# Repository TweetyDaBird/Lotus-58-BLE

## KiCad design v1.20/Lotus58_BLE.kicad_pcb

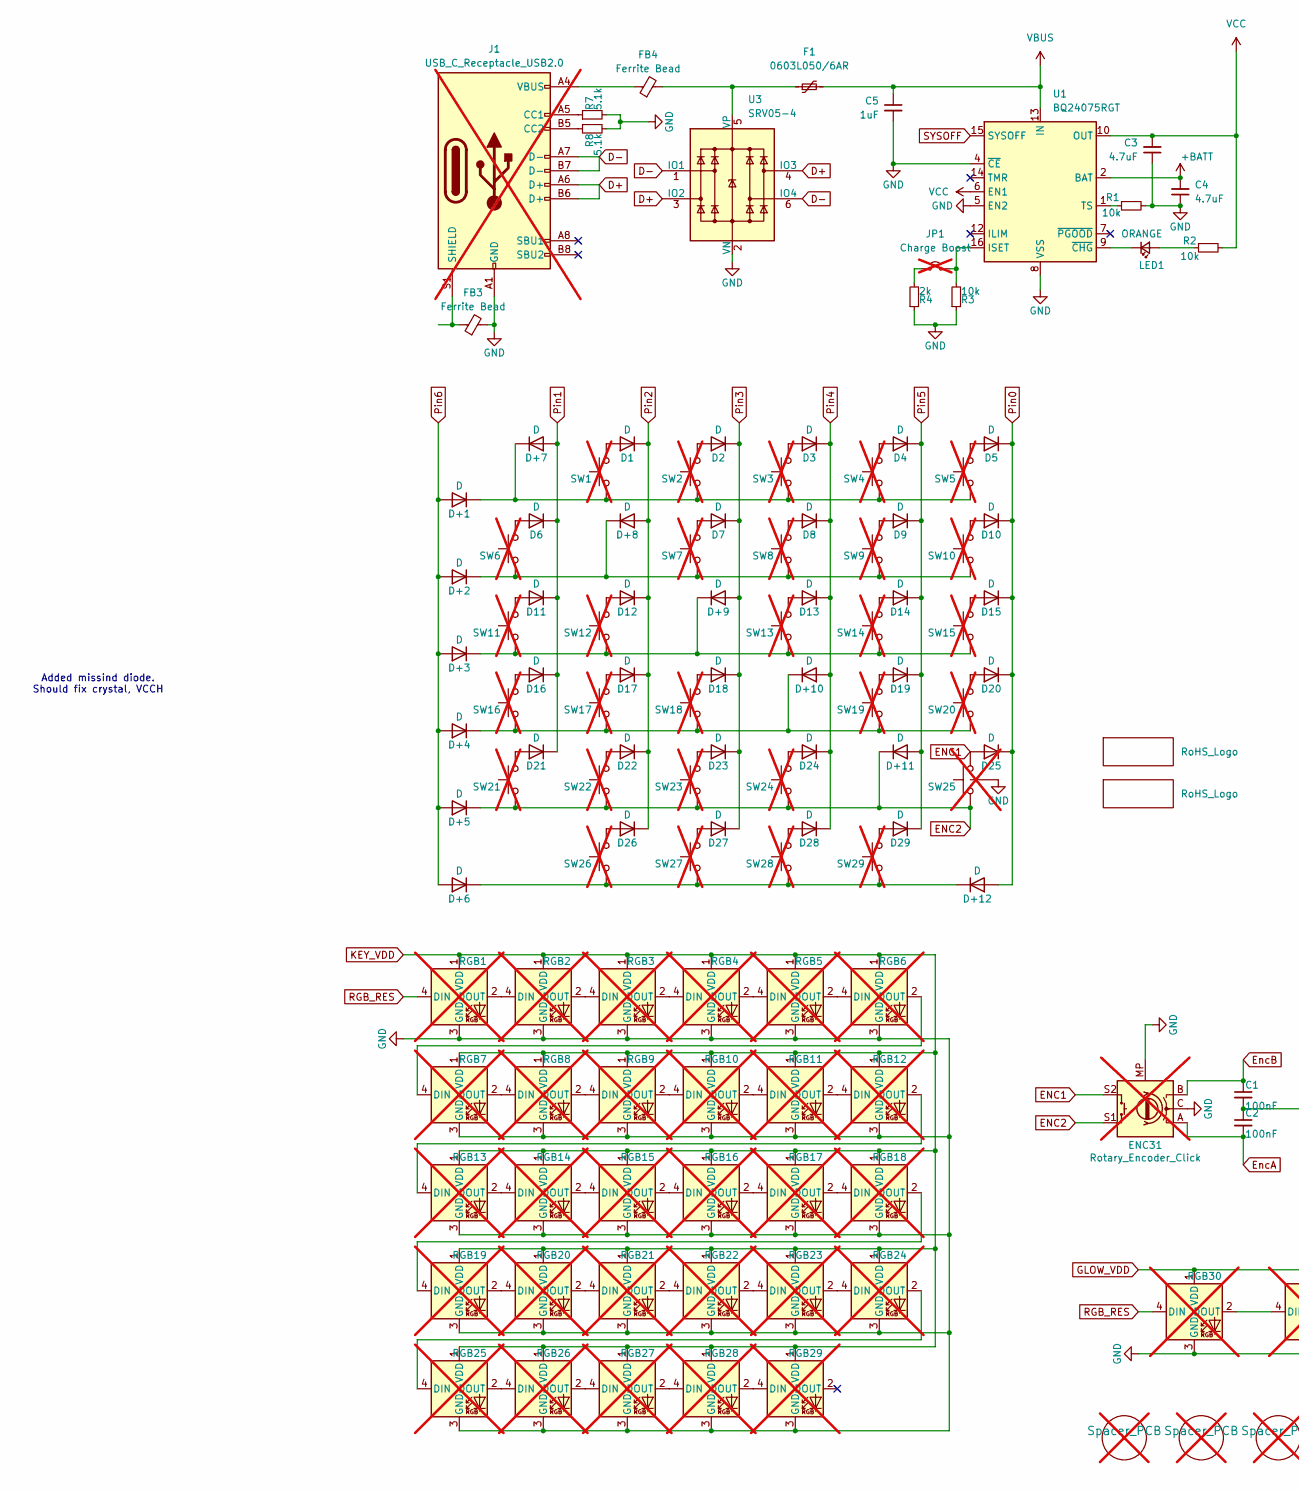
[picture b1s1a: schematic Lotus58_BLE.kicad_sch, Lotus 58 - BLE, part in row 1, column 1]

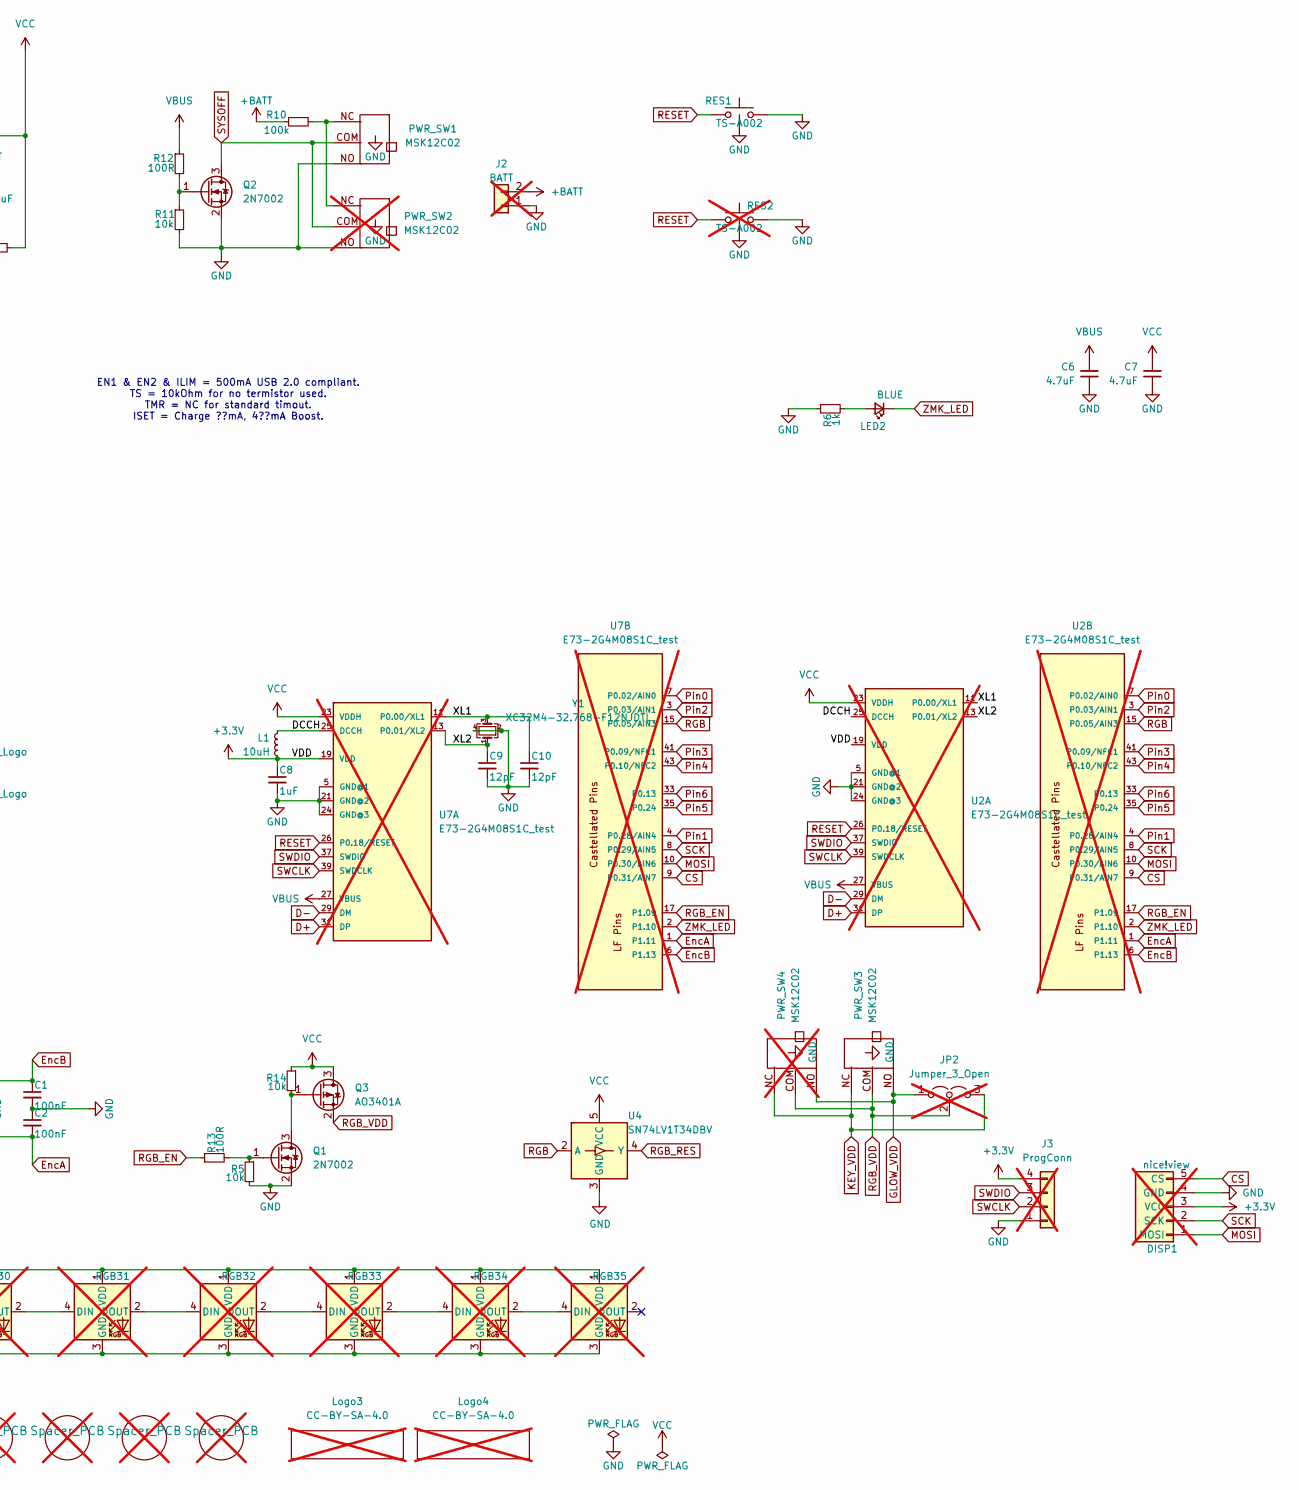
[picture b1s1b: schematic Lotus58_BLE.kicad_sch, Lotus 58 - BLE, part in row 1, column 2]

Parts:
C1, C2: 100nF; C_0402_1005Metric; LCSC C1525
C3, C4, C6, C7: 4.7uF; C_0402_1005Metric; LCSC C274416
C5, C8: 1uF; C_0402_1005Metric; LCSC C52923
C9, C10: 12pF; C_0402_1005Metric; LCSC C424835
D1, D2, D3, D4, D5, D6, D7, D8, D9, D10, D11, D12, D13, D14, D15, D16, D17, D18, D19, D20, D21, D22, D23, D24, D25, D26, D27, D28, D29: D; D_SOD-323; LCSC C2128
D+1, D+2, D+3, D+4, D+5, D+6, D+7, D+8, D+9, D+10, D+11, D+12: D; D_SOD-323; LCSC C2128
DISP1: nice!view; nice!view_doublesided; not fitted
ENC31: Rotary_Encoder_Click; Encoder_Alps_EC11E_Small; not fitted
F1: 0603L050/6AR; R_0603_1608Metric; LCSC Part # C163116
FB3, FB4: Ferrite Bead; C_0603_1608Metric_Pad1.08x0.95mm_HandSolder; LCSC C1002
H1, H2, H3, H4, H5: Spacer_PCB; Spacer PCB hole; not fitted
J1: USB_C_Receptacle_USB2.0; HRO_TYPE-C-31-M-12_double_sided; LCSC C963373; not fitted
J2: BATT; PinHeader_1x02_P2.00mm_Vertical; not fitted
J3: ProgConn; PinHeader_1x04_P2.00mm_Vertical; not fitted
JP1: Charge Boost; Jumper_min_v2; not fitted
JP2: Jumper_3_Open; SolderJumper-3_open_mini; not fitted
L1: 10uH; L_0603_1608Metric; LCSC C180941
LED1: ORANGE; LED_0402_1005Metric; LCSC C965791
LED2: BLUE; LED_0402_1005Metric; LCSC C131223
Logo1, Logo2: RoHS_Logo; RoHs
Logo3, Logo4: CC-BY-SA-4.0; CC_BY_SA_40; not fitted
PWR_SW1, PWR_SW3: MSK12C02
PWR_SW2, PWR_SW4: MSK12C02; not fitted
Q1, Q2: 2N7002; SOT-23; LCSC C916396
Q3: AO3401A; SOT-23; LCSC C15127
R1, R2, R3, R5, R11, R14: 10k; R_0402_1005Metric; LCSC C25744
R4: 2k; R_0402_1005Metric; LCSC C472865
R6: 1k; R_0402_1005Metric; LCSC C11702
R7, R8: 5.1k; R_0402_1005Metric; LCSC C25905
R10: 100k; R_0402_1005Metric; LCSC C2982964
R12, R13: 100R; R_0402_1005Metric; LCSC C226677
RES1: TS-A002; YTS-A002; LCSC C2888934
RES2: TS-A002; YTS-A002; LCSC C2888934; not fitted
RGB1, RGB2, RGB3, RGB4, RGB5, RGB6, RGB7, RGB8, RGB9, RGB10, RGB11, RGB12, RGB13, RGB14, RGB15, RGB16, RGB17, RGB18, RGB19, RGB20, RGB21, RGB22, RGB23, RGB24, RGB25, RGB26, RGB27, RGB28, RGB29: SK6812MINI-E; RGB_SK6812MINI-E_reversible_tight; not fitted
RGB30, RGB31, RGB32, RGB33, RGB34, RGB35: SK6812MINI-E; MX_SK6812MINI-E_REVERSIBLE_special_v2; not fitted
SW1, SW2, SW3, SW4, SW5, SW6, SW7, SW8, SW9, SW10, SW11, SW12, SW13, SW14, SW15, SW16, SW17, SW18, SW19, SW20, SW21, SW22, SW23, SW24, SW26, SW27, SW28, SW29: SW_Push; SW_MX_HotSwap_Reversible; not fitted
SW25: SW_Push; SW_MX_HotSwap_Reversible_FOR encoder; not fitted
U1: BQ24075RGT; VQFN-16-1EP_3x3mm_P0.5mm_EP1.6x1.6mm_ThermalVias; LCSC C15464
U2, U7: E73-2G4M08S1C_test; E73-2G4M08S1C_Castellated; not fitted
U3: SRV05-4; SOT-23-6; LCSC C558418
U4: SN74LV1T34DBV; SOT-23-5; LCSC Part # C100024
Y1: XC32M4-32.768-F12NJDTL; Crystal_SMD_3225-4Pin_3.2x2.5mm; LCSC C5119018

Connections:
+3.3V: C8.1, DISP1.3 (VCC), J3.4, L1.2, U2.19 (VDD), U7.19 (VDD)
+BATT: C4.2, J2.2, R10.1, U1.2 (BAT), U1.3 (BAT)
/DCCH: L1.1, U2.25 (DCCH), U7.25 (DCCH)
/XL1: C10.1, U2.11 (P0.00/XL1), U7.11 (P0.00/XL1), Y1.3
/XL2: C9.1, U2.13 (P0.01/XL2), U7.13 (P0.01/XL2), Y1.1
CS: DISP1.5 (CS), U2.9 (P0.31/AIN7), U7.9 (P0.31/AIN7)
D+: J1.A6 (D+), J1.B6 (D+), U2.31 (DP), U3.3 (IO2), U3.4 (IO3), U7.31 (DP)
D-: J1.A7 (D-), J1.B7 (D-), U2.29 (DM), U3.1 (IO1), U3.6 (IO4), U7.29 (DM)
ENC1: D25.2 (A), ENC31.S2, SW25.1
ENC2: D+5.1 (K), D+11.1 (K), ENC31.S1, SW21.2, SW22.2, SW23.2, SW24.2, SW25.2
EncA: C2.2, ENC31.A, U2.1 (P1.11), U7.1 (P1.11)
EncB: C1.1, ENC31.B, U2.6 (P1.13), U7.6 (P1.13)
GLOW_VDD: JP2.1 (A), PWR_SW3.NO, PWR_SW4.NO, RGB30.1 (VDD), RGB31.1 (VDD), RGB32.1 (VDD), RGB33.1 (VDD), RGB34.1 (VDD), RGB35.1 (VDD)
GND: C1.2, C2.1, C3.1, C4.1, C5.2, C6.1, C7.1, C8.2, C9.2, C10.2, DISP1.4 (GND), ENC31.C, ENC31.MP (GND), FB3.2, J1.A1 (GND), J1.A12 (GND), J1.B1 (GND), J1.B12 (GND), J2.1, J3.1, PWR_SW1.MP (GND), PWR_SW1.NO, PWR_SW2.MP (GND), PWR_SW2.NO, PWR_SW3.MP (GND), PWR_SW4.MP (GND), Q1.2 (S), Q2.2 (S), R1.2, R3.1, R4.1, R5.2, R6.1, R7.2, R8.2, R11.2, RES1.1, RES1.3, RES2.2, RES2.3, RGB1.3 (GND), RGB2.3 (GND), RGB3.3 (GND), RGB4.3 (GND), RGB5.3 (GND), RGB6.3 (GND), RGB7.3 (GND), RGB8.3 (GND), RGB9.3 (GND), RGB10.3 (GND), RGB11.3 (GND), RGB12.3 (GND), RGB13.3 (GND), RGB14.3 (GND), RGB15.3 (GND), RGB16.3 (GND), RGB17.3 (GND), RGB18.3 (GND), RGB19.3 (GND), RGB20.3 (GND), RGB21.3 (GND), RGB22.3 (GND), RGB23.3 (GND), RGB24.3 (GND), RGB25.3 (GND), RGB26.3 (GND), RGB27.3 (GND), RGB28.3 (GND), RGB29.3 (GND), RGB30.3 (GND), RGB31.3 (GND), RGB32.3 (GND), RGB33.3 (GND), RGB34.3 (GND), RGB35.3 (GND), SW25.3, U1.4 (~CE), U1.5 (EN2), U1.8 (VSS), U1.17 (VSS), U2.5 (GND@1), U2.21 (GND@2), U2.24 (GND@3), U3.2 (VN), U4.3 (GND), U7.5 (GND@1), U7.21 (GND@2), U7.24 (GND@3), Y1.2, Y1.4
KEY_VDD: JP2.3 (B), PWR_SW3.NC, PWR_SW4.NC, RGB1.1 (VDD), RGB2.1 (VDD), RGB3.1 (VDD), RGB4.1 (VDD), RGB5.1 (VDD), RGB6.1 (VDD), RGB7.1 (VDD), RGB8.1 (VDD), RGB9.1 (VDD), RGB10.1 (VDD), RGB11.1 (VDD), RGB12.1 (VDD), RGB13.1 (VDD), RGB14.1 (VDD), RGB15.1 (VDD), RGB16.1 (VDD), RGB17.1 (VDD), RGB18.1 (VDD), RGB19.1 (VDD), RGB20.1 (VDD), RGB21.1 (VDD), RGB22.1 (VDD), RGB23.1 (VDD), RGB24.1 (VDD), RGB25.1 (VDD), RGB26.1 (VDD), RGB27.1 (VDD), RGB28.1 (VDD), RGB29.1 (VDD)
MOSI: DISP1.1 (MOSI), U2.10 (P0.30/AIN6), U7.10 (P0.30/AIN6)
unnamed: D1.2 (A), SW1.1
unnamed: D2.2 (A), SW2.1
unnamed: D3.2 (A), SW3.1
unnamed: D4.2 (A), SW4.1
unnamed: D5.2 (A), SW5.1
unnamed: D6.2 (A), SW6.1
unnamed: D7.2 (A), SW7.1
unnamed: D8.2 (A), SW8.1
unnamed: D9.2 (A), SW9.1
unnamed: D10.2 (A), SW10.1
unnamed: D11.2 (A), SW11.1
unnamed: D12.2 (A), SW12.1
unnamed: D13.2 (A), SW13.1
unnamed: D14.2 (A), SW14.1
unnamed: D15.2 (A), SW15.1
unnamed: D16.2 (A), SW16.1
unnamed: D17.2 (A), SW17.1
unnamed: D18.2 (A), SW18.1
unnamed: D19.2 (A), SW19.1
unnamed: D20.2 (A), SW20.1
unnamed: D21.2 (A), SW21.1
unnamed: D22.2 (A), SW22.1
unnamed: D23.2 (A), SW23.1
unnamed: D24.2 (A), SW24.1
unnamed: D26.2 (A), SW26.1
unnamed: D27.2 (A), SW27.1
unnamed: D28.2 (A), SW28.1
unnamed: D29.2 (A), SW29.1
unnamed: D+1.1 (K), D+7.1 (K), SW1.2, SW2.2, SW3.2, SW4.2, SW5.2
unnamed: D+2.1 (K), D+8.1 (K), SW6.2, SW7.2, SW8.2, SW9.2, SW10.2
unnamed: D+3.1 (K), D+9.1 (K), SW11.2, SW12.2, SW13.2, SW14.2, SW15.2
unnamed: D+4.1 (K), D+10.1 (K), SW16.2, SW17.2, SW18.2, SW19.2, SW20.2
unnamed: D+6.1 (K), D+12.1 (K), SW26.2, SW27.2, SW28.2, SW29.2
unnamed: FB4.1, J1.A4 (VBUS), J1.A9 (VBUS), J1.B4 (VBUS), J1.B9 (VBUS)
unnamed: J1.A5 (CC1), R7.1
unnamed: J1.B5 (CC2), R8.1
unnamed: FB3.1, J1.S1 (SHIELD)
unnamed: JP1.1 (A), R4.2
unnamed: JP1.2 (B), R3.2, U1.16 (ISET)
unnamed: LED1.2 (A), R2.1
unnamed: LED1.1 (K), U1.9 (~CHG)
unnamed: LED2.2 (A), R6.2
unnamed: PWR_SW1.NC, PWR_SW2.NC, R10.2
unnamed: Q1.3 (D), Q3.1 (G), R14.2
unnamed: Q1.1 (G), R5.1, R13.2
unnamed: Q2.1 (G), R11.1, R12.2
unnamed: RGB1.2 (DOUT), RGB2.4 (DIN)
unnamed: RGB2.2 (DOUT), RGB3.4 (DIN)
unnamed: RGB3.2 (DOUT), RGB4.4 (DIN)
unnamed: RGB4.2 (DOUT), RGB5.4 (DIN)
unnamed: RGB5.2 (DOUT), RGB6.4 (DIN)
unnamed: RGB6.2 (DOUT), RGB7.4 (DIN)
unnamed: RGB7.2 (DOUT), RGB8.4 (DIN)
unnamed: RGB8.2 (DOUT), RGB9.4 (DIN)
unnamed: RGB9.2 (DOUT), RGB10.4 (DIN)
unnamed: RGB10.2 (DOUT), RGB11.4 (DIN)
unnamed: RGB11.2 (DOUT), RGB12.4 (DIN)
unnamed: RGB12.2 (DOUT), RGB13.4 (DIN)
unnamed: RGB13.2 (DOUT), RGB14.4 (DIN)
unnamed: RGB14.2 (DOUT), RGB15.4 (DIN)
unnamed: RGB15.2 (DOUT), RGB16.4 (DIN)
unnamed: RGB16.2 (DOUT), RGB17.4 (DIN)
unnamed: RGB17.2 (DOUT), RGB18.4 (DIN)
unnamed: RGB18.2 (DOUT), RGB19.4 (DIN)
unnamed: RGB19.2 (DOUT), RGB20.4 (DIN)
unnamed: RGB20.2 (DOUT), RGB21.4 (DIN)
unnamed: RGB21.2 (DOUT), RGB22.4 (DIN)
unnamed: RGB22.2 (DOUT), RGB23.4 (DIN)
unnamed: RGB23.2 (DOUT), RGB24.4 (DIN)
unnamed: RGB24.2 (DOUT), RGB25.4 (DIN)
unnamed: RGB25.2 (DOUT), RGB26.4 (DIN)
unnamed: RGB26.2 (DOUT), RGB27.4 (DIN)
unnamed: RGB27.2 (DOUT), RGB28.4 (DIN)
unnamed: RGB28.2 (DOUT), RGB29.4 (DIN)
unnamed: RGB30.2 (DOUT), RGB31.4 (DIN)
unnamed: RGB31.2 (DOUT), RGB32.4 (DIN)
unnamed: RGB32.2 (DOUT), RGB33.4 (DIN)
unnamed: RGB33.2 (DOUT), RGB34.4 (DIN)
unnamed: RGB34.2 (DOUT), RGB35.4 (DIN)
unnamed: R1.1, U1.1 (TS)
unnamed: F1.1, FB4.2, U3.5 (VP)
Pin0: D5.1 (K), D10.1 (K), D15.1 (K), D20.1 (K), D25.1 (K), D+12.2 (A), U2.7 (P0.02/AIN0), U7.7 (P0.02/AIN0)
Pin1: D6.1 (K), D11.1 (K), D16.1 (K), D21.1 (K), D+7.2 (A), U2.4 (P0.28/AIN4), U7.4 (P0.28/AIN4)
Pin2: D1.1 (K), D12.1 (K), D17.1 (K), D22.1 (K), D26.1 (K), D+8.2 (A), U2.3 (P0.03/AIN1), U7.3 (P0.03/AIN1)
Pin3: D2.1 (K), D7.1 (K), D18.1 (K), D23.1 (K), D27.1 (K), D+9.2 (A), U2.41 (P0.09/NFC1), U7.41 (P0.09/NFC1)
Pin4: D3.1 (K), D8.1 (K), D13.1 (K), D24.1 (K), D28.1 (K), D+10.2 (A), U2.43 (P0.10/NFC2), U7.43 (P0.10/NFC2)
Pin5: D4.1 (K), D9.1 (K), D14.1 (K), D19.1 (K), D29.1 (K), D+11.2 (A), U2.35 (P0.24), U7.35 (P0.24)
Pin6: D+1.2 (A), D+2.2 (A), D+3.2 (A), D+4.2 (A), D+5.2 (A), D+6.2 (A), U2.33 (P0.13), U7.33 (P0.13)
RESET: RES1.2, RES2.1, U2.26 (P0.18/RESET), U7.26 (P0.18/RESET)
RGB: U2.15 (P0.05/AIN3), U4.2 (A), U7.15 (P0.05/AIN3)
RGB_EN: R13.1, U2.17 (P1.09), U7.17 (P1.09)
RGB_RES: RGB1.4 (DIN), RGB30.4 (DIN), U4.4 (Y)
RGB_VDD: JP2.2 (C), PWR_SW3.COM, PWR_SW4.COM, Q3.2 (S)
SCK: DISP1.2 (SCK), U2.8 (P0.29/AIN5), U7.8 (P0.29/AIN5)
SWCLK: J3.2, U2.39 (SWDCLK), U7.39 (SWDCLK)
SWDIO: J3.3, U2.37 (SWDIO), U7.37 (SWDIO)
SYSOFF: PWR_SW1.COM, PWR_SW2.COM, Q2.3 (D), U1.15 (SYSOFF)
VBUS: C5.1, C6.2, F1.2, R12.1, U1.13 (IN), U2.27 (VBUS), U7.27 (VBUS)
VCC: C3.2, C7.2, Q3.3 (D), R2.2, R14.1, U1.6 (EN1), U1.10 (OUT), U1.11 (OUT), U2.23 (VDDH), U4.5 (VCC), U7.23 (VDDH)
ZMK_LED: LED2.1 (K), U2.2 (P1.10), U7.2 (P1.10)

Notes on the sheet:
EN1 & EN2 & ILIM = 500mA USB 2.0 compliant. TS = 10kOhm for no termistor used. TMR = NC for standard timout. ISET = Charge ??mA, 4??mA Boost.
Added missind diode. Should fix crystal, VCCH

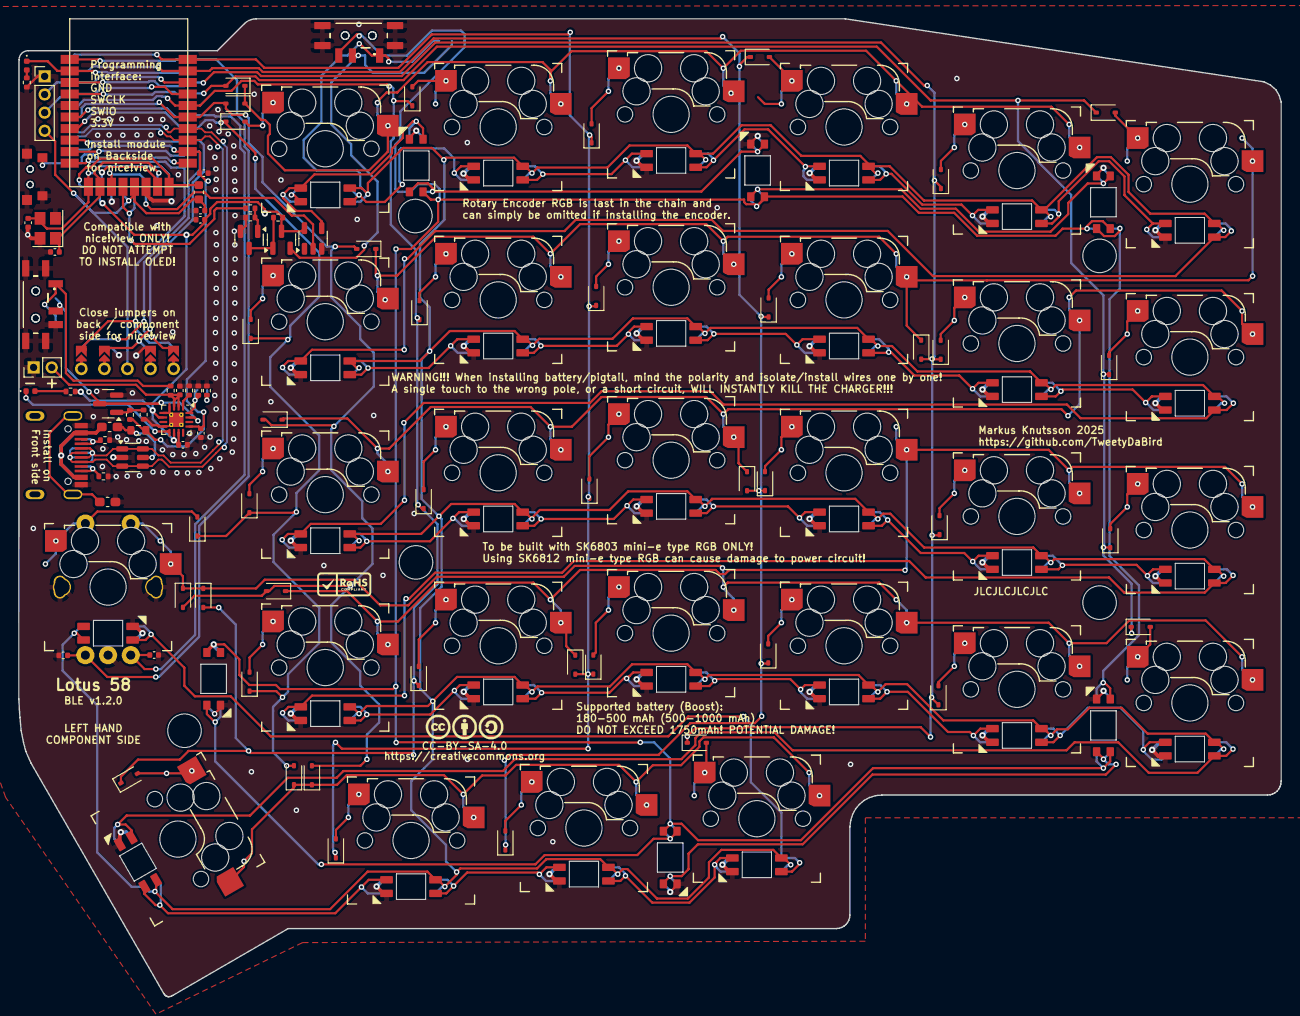
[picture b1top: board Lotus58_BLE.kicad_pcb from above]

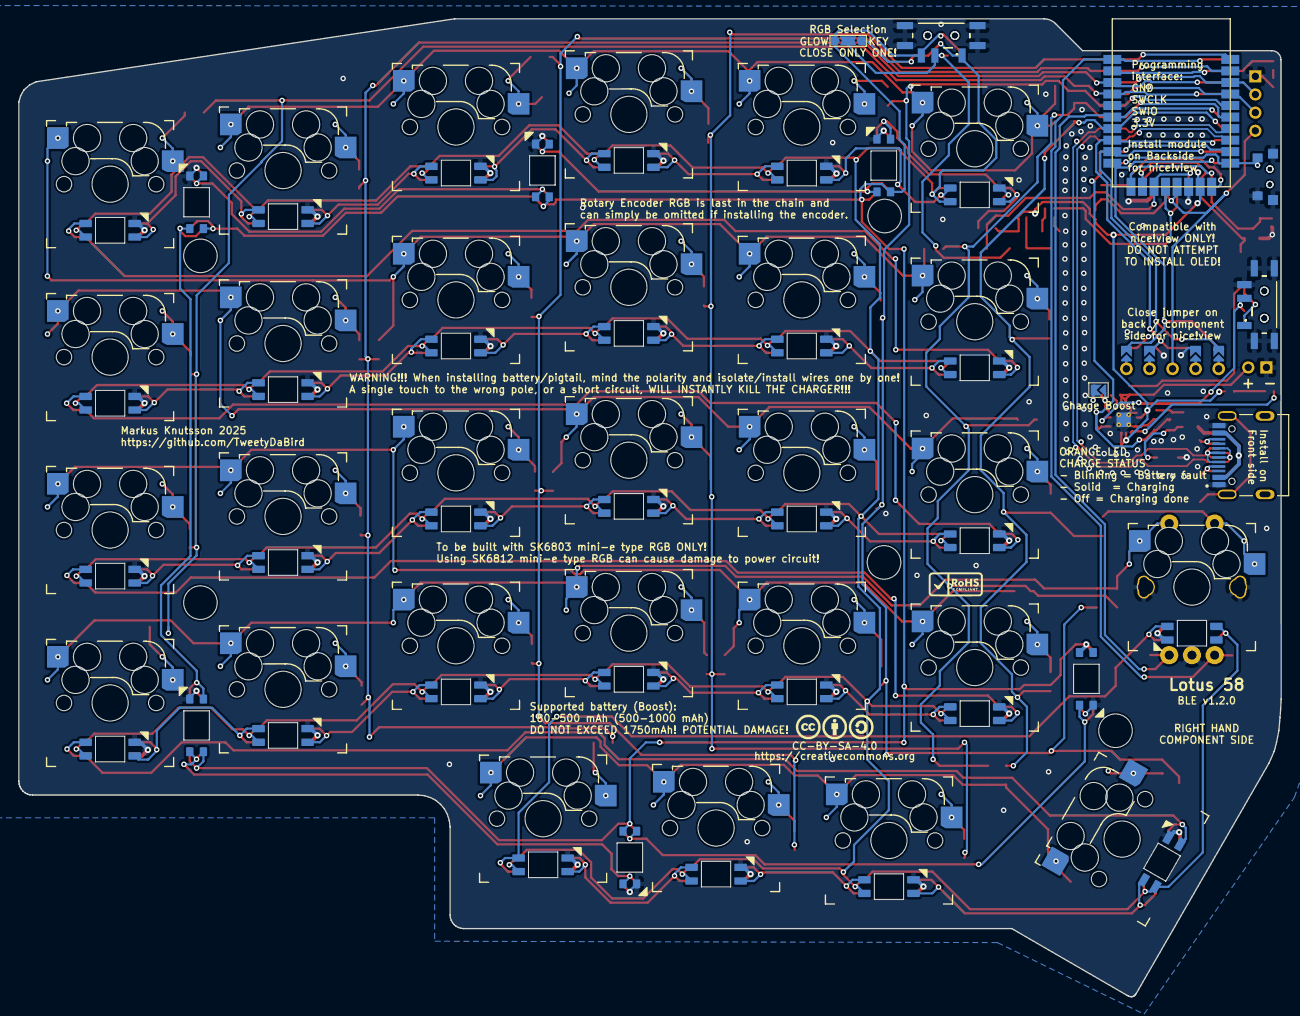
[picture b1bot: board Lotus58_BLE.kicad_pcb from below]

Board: 2 copper layers, 139.1 x 107.7 mm, 165 parts (9 on the bottom side), 116 nets.

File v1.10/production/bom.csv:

Designator,Footprint,Quantity,Value,LCSC Part #
"C1, C2",0402,2,100nF,C1525
"C10, C9",0402,2,12pF,C424835
"C3, C4, C6, C7",0402,4,4.7uF,C274416
"C5, C8",0402,2,1uF,C52923
"D+1, D+10, D+11, D+12, D+2, D+3, D+4, D+5, D+6, D+7, D+8, D+9, D1, D10, D11, D12, D13, D14, D15, D16, D17, D18, D19, D2, D20, D21, D22, D23, D24, D25, D26, D27, D28, D29, D3, D4, D5, D6, D7, D8, D9",D_SOD-323,41,D,C2128
F1,0603,1,0603L050/6AR,C163116
"FB3, FB4",0603,2,Ferrite Bead,C1002
J1,HRO_TYPE-C-31-M-12_double_sided,1,USB_C_Receptacle_USB2.0,C963373
L1,0603,1,10uH,C180941
LED1,0402,1,ORANGE,C965791
LED2,0402,1,BLUE,C131223
PWR_SW1,MSK12C02,1,MSK12C02,
"Q1, Q2",SOT-23,2,2N7002,C916396
Q3,SOT-23,1,AO3401A,C15127
"R1, R11, R14, R2, R3, R5",0402,6,10k,C25744
R10,0402,1,100k,C2982964
"R12, R13",0402,2,100R,C226677
R4,0402,1,2k,C472865
R6,0402,1,1k,C11702
"R7, R8",0402,2,5.1k,C25905
RES1,YTS-A002,1,TS-A002,C2888934
U1,VQFN-16-1EP_3x3mm_P0.5mm_EP1.6x1.6mm_ThermalVias,1,BQ24075RGT,C15464
U3,SOT-23-6,1,SRV05-4,C558418
U4,SOT-23-5,1,SN74LV1T34DBV,C100024
U7,E73-2G4M08S1C_Castellated,1,E73-2G4M08S1C_test,
Y1,Crystal_SMD_3225-4Pin_3.2x2.5mm,1,XC32M4-32.768-F12NJDTL,C5119018

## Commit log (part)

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2024-11-15 Initial Design
2024-11-15 Added stepfiles
2024-11-15 Add Schematic as PDF
2025-06-15 v1.1.0
2025-06-25 V1.2.0
    Added RGB selector

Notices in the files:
v1.00/Lotus58_BLE.kicad_sch:
Licensed under Creative Commons BY-SA 4.0 International
